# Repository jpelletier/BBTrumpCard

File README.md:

The Big Beautiful Trump Card is a clone of Steve Ciarcia's Trump Card based on the Zilog Z8001 CPU.
The project is released under OSHW.

To simplify the project, I use more recent components such as a CPLD to contain the glue logic and a memory chip to replace the dynamic memory.
The project is in the prototype stage for now. The PCB is at version 1, but untested yet.

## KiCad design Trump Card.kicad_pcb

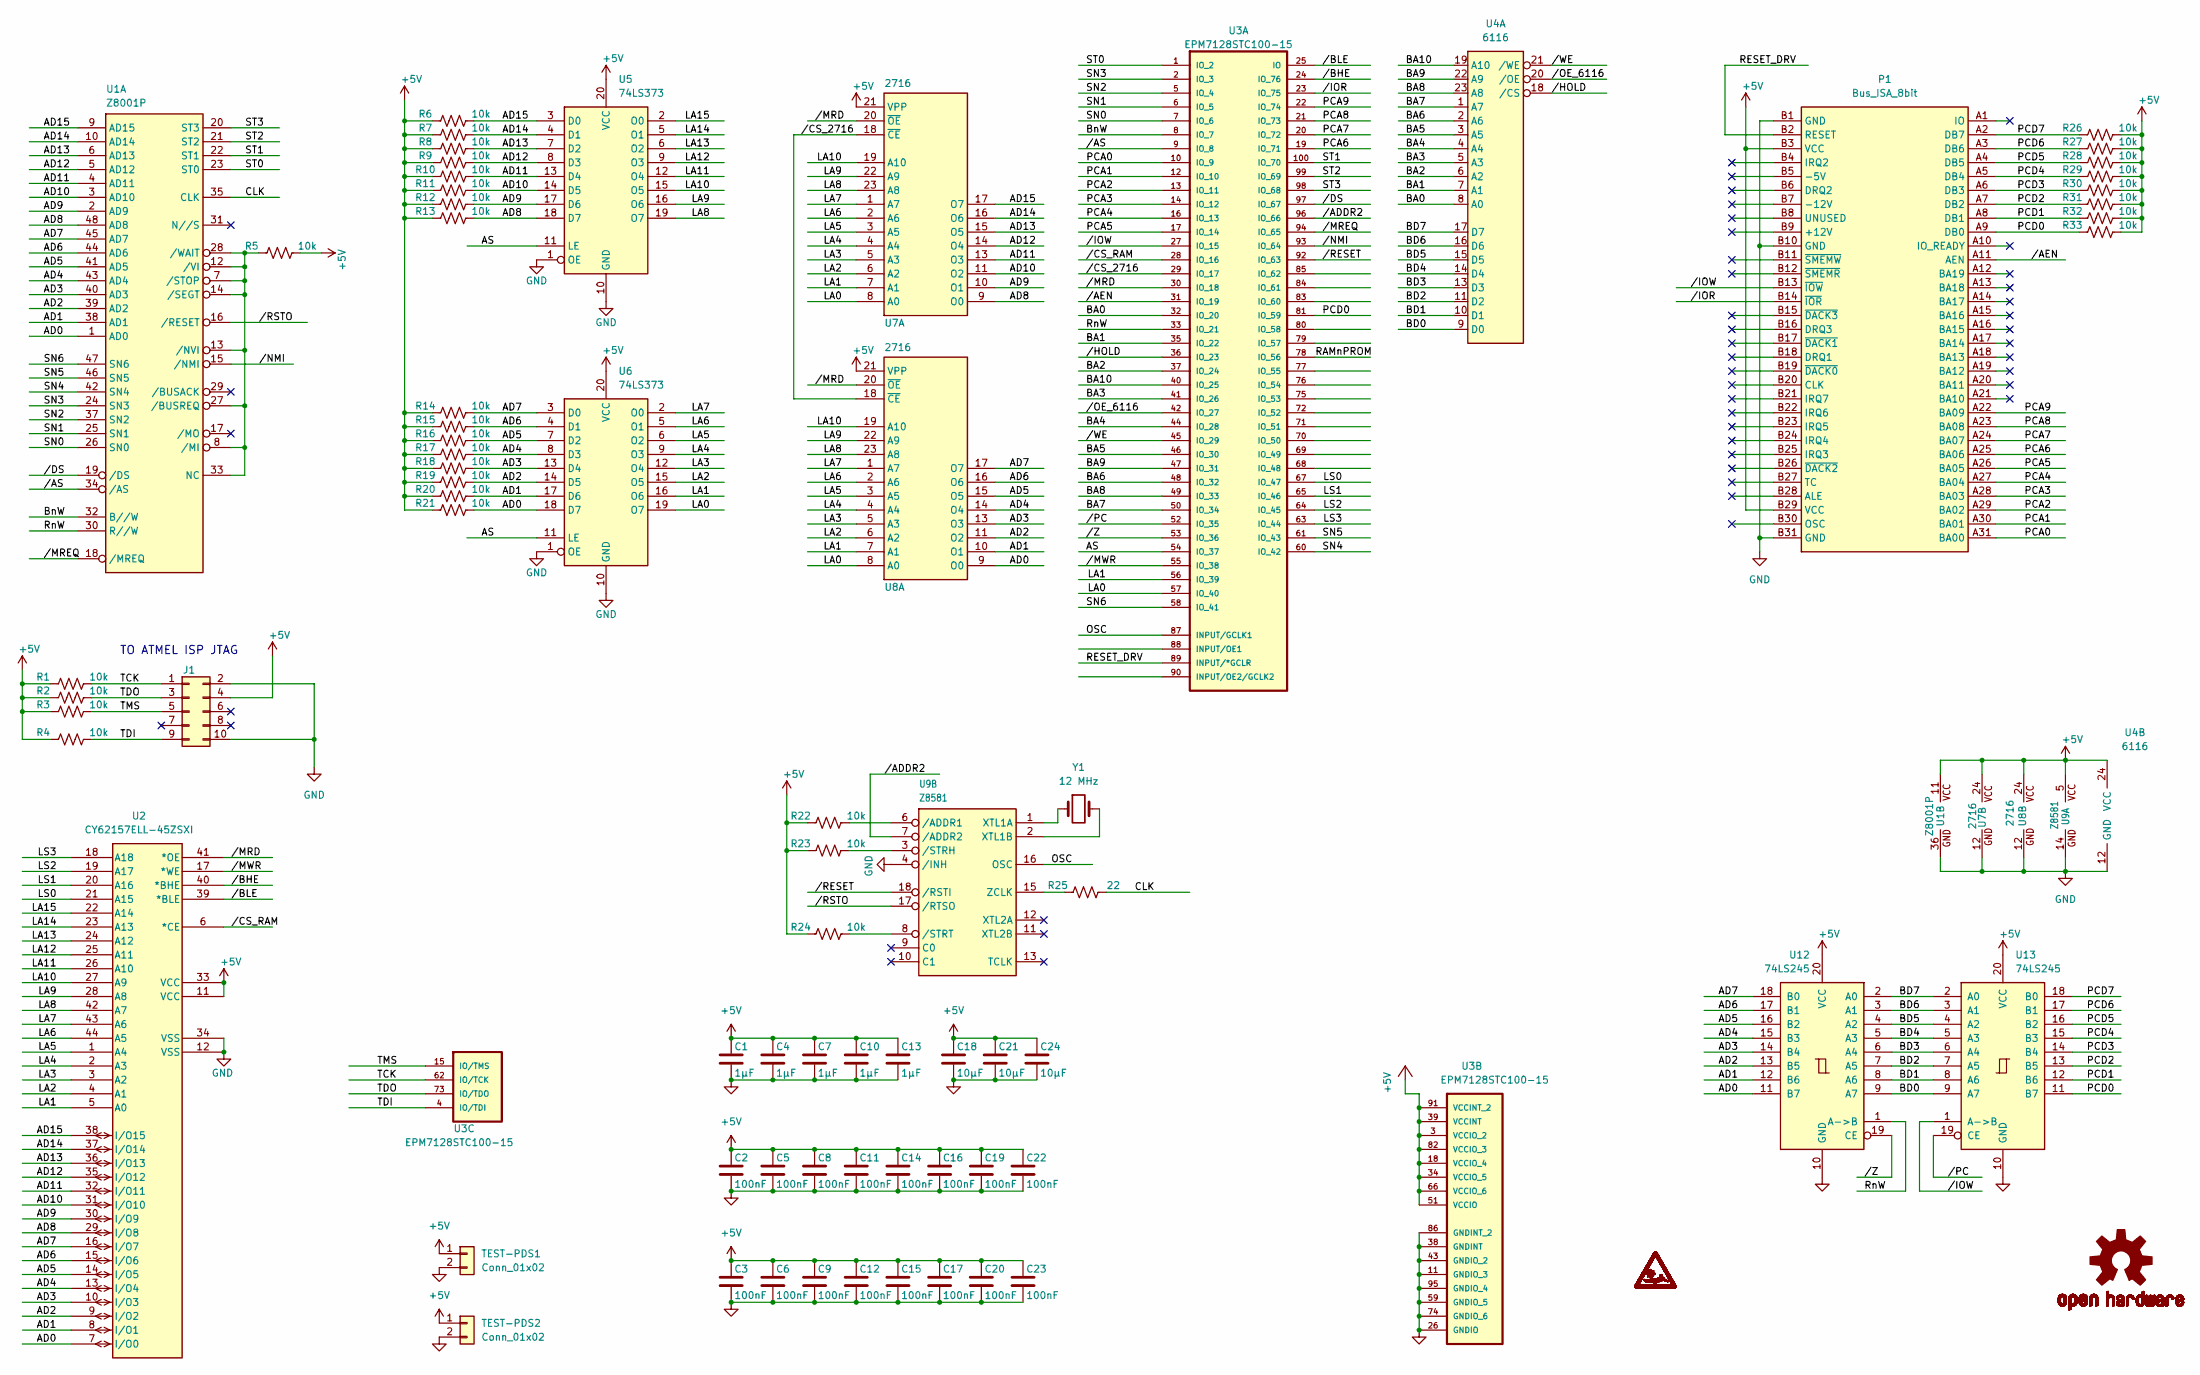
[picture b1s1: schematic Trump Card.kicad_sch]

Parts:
C1, C4, C7, C10, C13: 1µF; C_0805_2012Metric_Pad1.18x1.45mm_HandSolder
C2, C3, C5, C6, C8, C9, C11, C12, C14, C15, C16, C17, C19, C20, C22, C23: 100nF; C_0603_1608Metric_Pad1.08x0.95mm_HandSolder
C18, C21, C24: 10µF; C_0805_2012Metric_Pad1.18x1.45mm_HandSolder
J1: Conn_02x05_Odd_Even; PinHeader_2x05_P2.54mm_Vertical
LOGO1: OSHW-LOGOM; OSHW-LOGO-M
P1: Bus_ISA_8bit; PC-XT-Short-6in
R1, R2, R3, R4, R5, R6, R7, R8, R9, R10, R11, R12, R13, R14, R15, R16, R17, R18, R19, R20, R21, R22, R23, R24, R26, R27, R28, R29, R30, R31, R32, R33: 10k; R_0603_1608Metric_Pad0.98x0.95mm_HandSolder
R25: 22; R_0603_1608Metric_Pad0.98x0.95mm_HandSolder
TEST-PDS1, TEST-PDS2: Conn_01x02; TEST_PDS
U1: Z8001P; DIP-48_W15.24mm
U2: CY62157ELL-45ZSXI; TSOP-II-44_10.16x18.41mm_P0.8mm
U3: EPM7128STC100-15; QFP50P1600X1600X120-100N; MPN EPM7128STC100-15
U4: 6116; DIP-24_18.0mmx34.29mm_W15.24mm
U5, U6: 74LS373; DIP-20_W7.62mm
U7, U8: 2716; DIP-24_18.0mmx34.29mm_W15.24mm
U9: Z8581; DIP-18_W7.62mm
U11: PHYSNOCT_PHYSNOCT; PHYSNOCT
U12, U13: 74LS245; DIP-20_W7.62mm
Y1: 12 MHz; Crystal_HC49-U_Vertical

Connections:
+5V: C1.1, C2.1, C3.1, C4.1, C5.1, C6.1, C7.1, C8.1, C9.1, C10.1, C11.1, C12.1, C13.1, C14.1, C15.1, C16.1, C17.1, C18.1, C19.1, C20.1, C21.1, C22.1, C23.1, C24.1, J1.4, P1.B3 (VCC), P1.B29 (VCC), R1.1, R2.1, R3.1, R4.1, R5.2, R6.1, R7.1, R8.1, R9.1, R10.1, R11.1, R12.1, R13.1, R14.1, R15.1, R16.1, R17.1, R18.1, R19.1, R20.1, R21.1, R22.1, R23.1, R24.1, R26.2, R27.2, R28.2, R29.2, R30.2, R31.2, R32.2, R33.2, TEST-PDS1.1, TEST-PDS2.1, U1.11 (VCC), U2.11 (VCC), U2.33 (VCC), U3.3 (VCCIO_2), U3.18 (VCCIO_4), U3.34 (VCCIO_5), U3.39 (VCCINT), U3.51 (VCCIO), U3.66 (VCCIO_6), U3.82 (VCCIO_3), U3.91 (VCCINT_2), U4.24 (VCC), U5.20 (VCC), U6.20 (VCC), U7.21 (VPP), U7.24 (VCC), U8.21 (VPP), U8.24 (VCC), U9.5 (VCC), U12.20 (VCC), U13.20 (VCC)
/AD0: R21.2, U1.1 (AD0), U2.7 (I/O0), U6.18 (D7), U8.9 (O0), U12.11 (B7)
/AD1: R20.2, U1.38 (AD1), U2.8 (I/O1), U6.17 (D6), U8.10 (O1), U12.12 (B6)
/AD2: R19.2, U1.39 (AD2), U2.9 (I/O2), U6.14 (D5), U8.11 (O2), U12.13 (B5)
/AD3: R18.2, U1.40 (AD3), U2.10 (I/O3), U6.13 (D4), U8.13 (O3), U12.14 (B4)
/AD4: R17.2, U1.43 (AD4), U2.13 (I/O4), U6.8 (D3), U8.14 (O4), U12.15 (B3)
/AD5: R16.2, U1.41 (AD5), U2.14 (I/O5), U6.7 (D2), U8.15 (O5), U12.16 (B2)
/AD6: R15.2, U1.44 (AD6), U2.15 (I/O6), U6.4 (D1), U8.16 (O6), U12.17 (B1)
/AD7: R14.2, U1.45 (AD7), U2.16 (I/O7), U6.3 (D0), U8.17 (O7), U12.18 (B0)
/AD8: R13.2, U1.48 (AD8), U2.29 (I/O8), U5.18 (D7), U7.9 (O0)
/AD9: R12.2, U1.2 (AD9), U2.30 (I/O9), U5.17 (D6), U7.10 (O1)
/AD10: R11.2, U1.3 (AD10), U2.31 (I/O10), U5.14 (D5), U7.11 (O2)
/AD11: R10.2, U1.4 (AD11), U2.32 (I/O11), U5.13 (D4), U7.13 (O3)
/AD12: R9.2, U1.5 (AD12), U2.35 (I/O12), U5.8 (D3), U7.14 (O4)
/AD13: R8.2, U1.6 (AD13), U2.36 (I/O13), U5.7 (D2), U7.15 (O5)
/AD14: R7.2, U1.10 (AD14), U2.37 (I/O14), U5.4 (D1), U7.16 (O6)
/AD15: R6.2, U1.9 (AD15), U2.38 (I/O15), U5.3 (D0), U7.17 (O7)
/AS: U3.54 (IO_37), U5.11 (LE), U6.11 (LE)
/BA0: U3.32 (IO_20), U4.8 (A0)
/BA1: U3.35 (IO_22), U4.7 (A1)
/BA2: U3.37 (IO_24), U4.6 (A2)
/BA3: U3.41 (IO_26), U4.5 (A3)
/BA4: U3.44 (IO_28), U4.4 (A4)
/BA5: U3.46 (IO_30), U4.3 (A5)
/BA6: U3.48 (IO_32), U4.2 (A6)
/BA7: U3.50 (IO_34), U4.1 (A7)
/BA8: U3.49 (IO_33), U4.23 (A8)
/BA9: U3.47 (IO_31), U4.22 (A9)
/BA10: U3.40 (IO_25), U4.19 (A10)
/BD0: U4.9 (D0), U12.9 (A7), U13.9 (A7)
/BD1: U4.10 (D1), U12.8 (A6), U13.8 (A6)
/BD2: U4.11 (D2), U12.7 (A5), U13.7 (A5)
/BD3: U4.13 (D3), U12.6 (A4), U13.6 (A4)
/BD4: U4.14 (D4), U12.5 (A3), U13.5 (A3)
/BD5: U4.15 (D5), U12.4 (A2), U13.4 (A2)
/BD6: U4.16 (D6), U12.3 (A1), U13.3 (A1)
/BD7: U4.17 (D7), U12.2 (A0), U13.2 (A0)
/BnW: U1.32 (B//W), U3.8 (IO_7)
/CLK: R25.2, U1.35 (CLK)
/LA0: U3.57 (IO_40), U6.19 (O7), U7.8 (A0), U8.8 (A0)
/LA1: U2.5 (A0), U3.56 (IO_39), U6.16 (O6), U7.7 (A1), U8.7 (A1)
/LA2: U2.4 (A1), U6.15 (O5), U7.6 (A2), U8.6 (A2)
/LA3: U2.3 (A2), U6.12 (O4), U7.5 (A3), U8.5 (A3)
/LA4: U2.2 (A3), U6.9 (O3), U7.4 (A4), U8.4 (A4)
/LA5: U2.1 (A4), U6.6 (O2), U7.3 (A5), U8.3 (A5)
/LA6: U2.44 (A5), U6.5 (O1), U7.2 (A6), U8.2 (A6)
/LA7: U2.43 (A6), U6.2 (O0), U7.1 (A7), U8.1 (A7)
/LA8: U2.42 (A7), U5.19 (O7), U7.23 (A8), U8.23 (A8)
/LA9: U2.28 (A8), U5.16 (O6), U7.22 (A9), U8.22 (A9)
/LA10: U2.27 (A9), U5.15 (O5), U7.19 (A10), U8.19 (A10)
/LA11: U2.26 (A10), U5.12 (O4)
/LA12: U2.25 (A11), U5.9 (O3)
/LA13: U2.24 (A12), U5.6 (O2)
/LA14: U2.23 (A13), U5.5 (O1)
/LA15: U2.22 (A14), U5.2 (O0)
/LS0: U2.21 (A15), U3.67 (IO_47)
/LS1: U2.20 (A16), U3.65 (IO_46)
/LS2: U2.19 (A17), U3.64 (IO_45)
/LS3: U2.18 (A18), U3.63 (IO_44)
/OSC: U3.87 (INPUT/GCLK1), U9.16 (OSC)
/PCA0: P1.A31 (BA00), U3.10 (IO_9)
/PCA1: P1.A30 (BA01), U3.12 (IO_10)
/PCA2: P1.A29 (BA02), U3.13 (IO_11)
/PCA3: P1.A28 (BA03), U3.14 (IO_12)
/PCA4: P1.A27 (BA04), U3.16 (IO_13)
/PCA5: P1.A26 (BA05), U3.17 (IO_14)
/PCA6: P1.A25 (BA06), U3.19 (IO_71)
/PCA7: P1.A24 (BA07), U3.20 (IO_72)
/PCA8: P1.A23 (BA08), U3.21 (IO_73)
/PCA9: P1.A22 (BA09), U3.22 (IO_74)
/PCD0: P1.A9 (DB0), R33.1, U3.81 (IO_59), U13.11 (B7)
/PCD1: P1.A8 (DB1), R32.1, U13.12 (B6)
/PCD2: P1.A7 (DB2), R31.1, U13.13 (B5)
/PCD3: P1.A6 (DB3), R30.1, U13.14 (B4)
/PCD4: P1.A5 (DB4), R29.1, U13.15 (B3)
/PCD5: P1.A4 (DB5), R28.1, U13.16 (B2)
/PCD6: P1.A3 (DB6), R27.1, U13.17 (B1)
/PCD7: P1.A2 (DB7), R26.1, U13.18 (B0)
/RAMnPROM: U3.78 (IO_56)
/RESET_DRV: P1.B2 (RESET), U3.89 (INPUT/*GCLR)
/RnW: U1.30 (R//W), U3.33 (IO_21), U12.1 (A->B)
/SN0: U1.26 (SN0), U3.7 (IO_6)
/SN1: U1.25 (SN1), U3.6 (IO_5)
/SN2: U1.37 (SN2), U3.5 (IO_4)
/SN3: U1.24 (SN3), U3.2 (IO_3)
/SN4: U1.42 (SN4), U3.60 (IO_42)
/SN5: U1.46 (SN5), U3.61 (IO_43)
/SN6: U1.47 (SN6), U3.58 (IO_41)
/ST0: U1.23 (ST0), U3.1 (IO_2)
/ST1: U1.22 (ST1), U3.100 (IO_70)
/ST2: U1.21 (ST2), U3.99 (IO_69)
/ST3: U1.20 (ST3), U3.98 (IO_68)
/TCK: J1.1, R1.2, U3.62 (IO/TCK)
/TDI: J1.9, R4.2, U3.4 (IO/TDI)
/TDO: J1.3, R2.2, U3.73 (IO/TDO)
/TMS: J1.5, R3.2, U3.15 (IO/TMS)
//ADDR2: U3.96 (IO_66), U9.7 (/ADDR2)
//AEN: P1.A11 (AEN), U3.31 (IO_19)
//AS: U1.34 (/AS), U3.9 (IO_8)
//BHE: U2.40 (*BHE), U3.24 (IO_76)
//BLE: U2.39 (*BLE), U3.25 (IO)
//CS_2716: U3.29 (IO_17), U7.18 (~CE), U8.18 (~CE)
//CS_RAM: U2.6 (*CE), U3.28 (IO_16)
//DS: U1.19 (/DS), U3.97 (IO_67)
//HOLD: U3.36 (IO_23), U4.18 (/CS)
//IOR: P1.B14 (~IOR), U3.23 (IO_75)
//IOW: P1.B13 (~IOW), U3.27 (IO_15), U13.1 (A->B)
//MRD: U2.41 (*OE), U3.30 (IO_18), U7.20 (~OE), U8.20 (~OE)
//MREQ: U1.18 (/MREQ), U3.94 (IO_65)
//MWR: U2.17 (*WE), U3.55 (IO_38)
//NMI: U1.15 (/NMI), U3.93 (IO_64)
//OE_6116: U3.42 (IO_27), U4.20 (/OE)
//PC: U3.52 (IO_35), U13.19 (CE)
//RESET: U3.92 (IO_63), U9.18 (/RSTI)
//RSTO: U1.16 (/RESET), U9.17 (/RTSO)
//WE: U3.45 (IO_29), U4.21 (/WE)
//Z: U3.53 (IO_36), U12.19 (CE)
GND: C1.2, C2.2, C3.2, C4.2, C5.2, C6.2, C7.2, C8.2, C9.2, C10.2, C11.2, C12.2, C13.2, C14.2, C15.2, C16.2, C17.2, C18.2, C19.2, C20.2, C21.2, C22.2, C23.2, C24.2, J1.2, J1.10, P1.B1 (GND), P1.B10 (GND), P1.B31 (GND), TEST-PDS1.2, TEST-PDS2.2, U1.36 (GND), U2.12 (VSS), U2.34 (VSS), U3.11 (GNDIO_3), U3.26 (GNDIO), U3.38 (GNDINT), U3.43 (GNDIO_2), U3.59 (GNDIO_5), U3.74 (GNDIO_6), U3.86 (GNDINT_2), U3.95 (GNDIO_4), U4.12 (GND), U5.1 (OE), U5.10 (GND), U6.1 (OE), U6.10 (GND), U7.12 (GND), U8.12 (GND), U9.4 (/INH), U9.14 (GND), U12.10 (GND), U13.10 (GND)
unnamed: R5.1, U1.7 (/STOP), U1.8 (/MI), U1.12 (/VI), U1.13 (/NVI), U1.14 (/SEGT), U1.27 (/BUSREQ), U1.28 (/WAIT), U1.33 (NC)
unnamed: U9.1 (XTL1A), Y1.1
unnamed: U9.2 (XTL1B), Y1.2
unnamed: R25.1, U9.15 (ZCLK)
unnamed: R22.2, U9.6 (/ADDR1)
unnamed: R23.2, U9.3 (/STRH)
unnamed: R24.2, U9.8 (/STRT)

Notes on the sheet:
TO ATMEL ISP JTAG

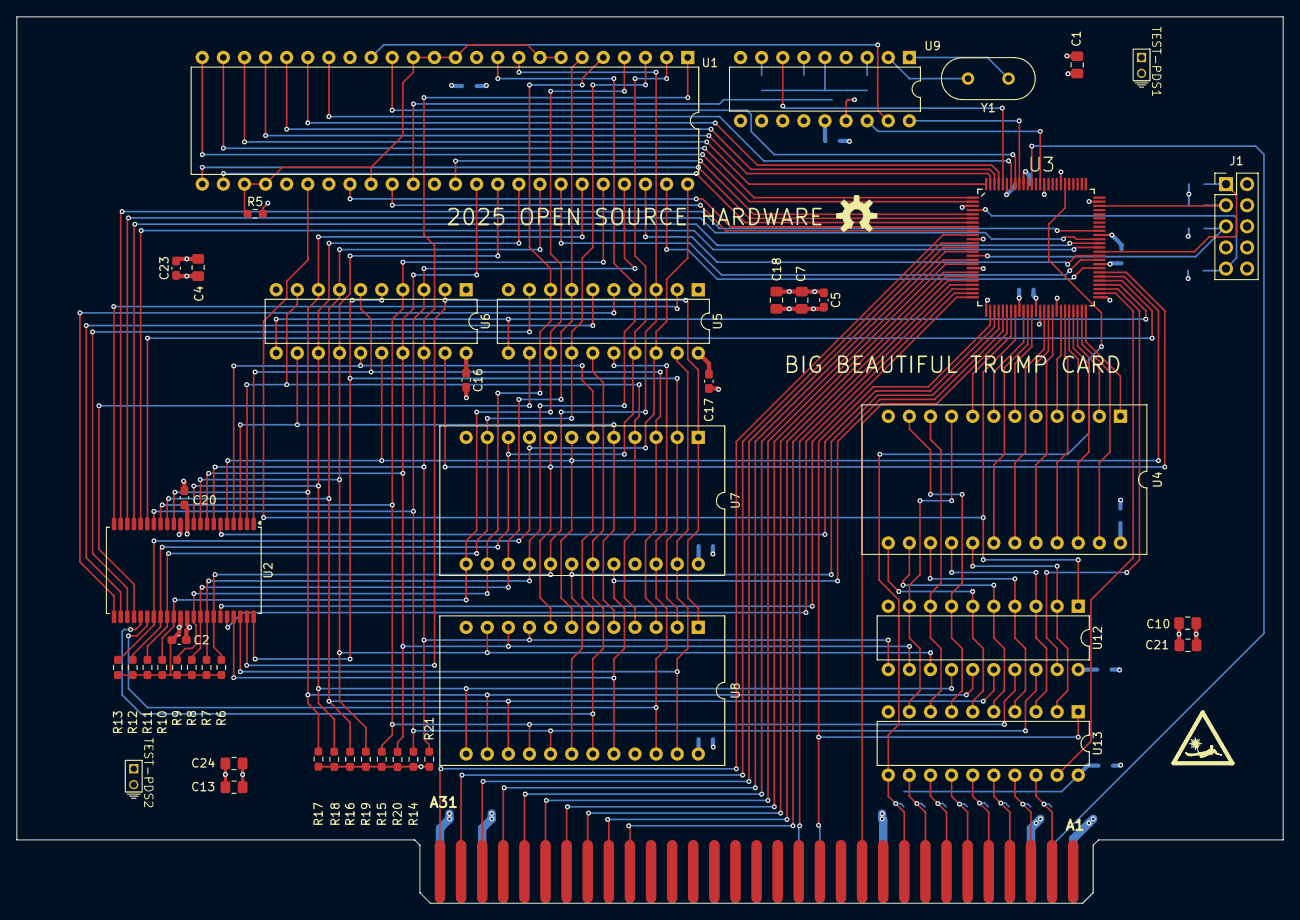
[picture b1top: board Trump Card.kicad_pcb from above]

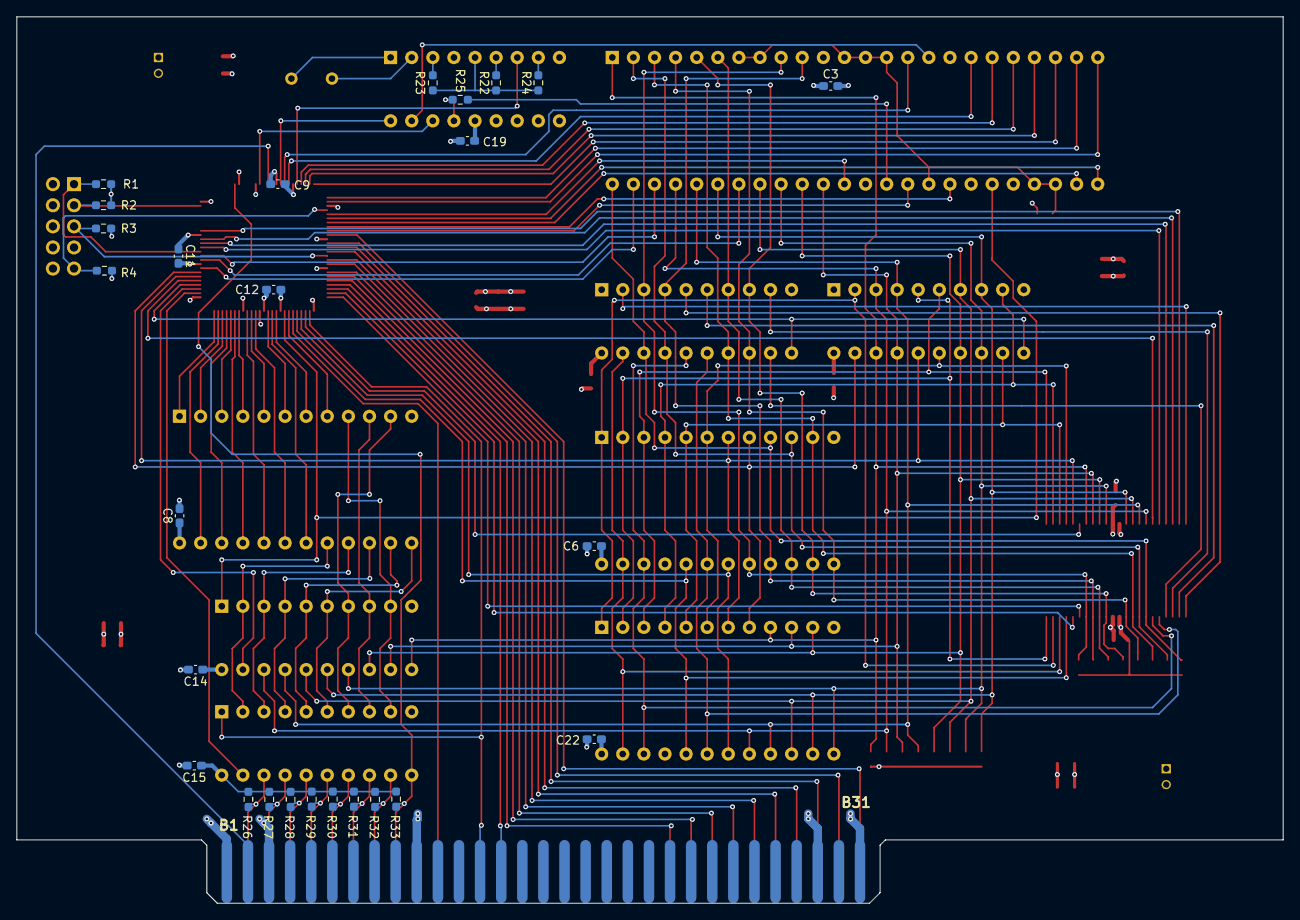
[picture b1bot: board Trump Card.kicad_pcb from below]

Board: 4 copper layers, 152.4 x 106.7 mm, 75 parts (26 on the bottom side), 124 nets.

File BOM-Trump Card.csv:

"Reference","Value","Qty","MPN","PACKAGE","SUPPLIER","Description","Manufacturer","Supplier2 Part Number","Supplier Part Number","SUPPLIER2"
"C1,C4,C7,C10,C13","1µF","5",,"0805",,"Unpolarized capacitor",,,,
"C2,C3,C5,C6,C8,C9,C11,C12,C14,C15,C16,C17,C19,C20,C22,C23","100nF","16",,"0603",,"Unpolarized capacitor",,,,
"C18,C21,C24","10µF","3",,"0805",,"Unpolarized capacitor",,,,
"J1","Conn_02x05_Odd_Even","1",,,"Digikey, AliExpress, eBay","Generic connector, double row, 02x05, odd/even pin numbering scheme (row 1 odd numbers, row 2 even numbers), script generated (kicad-library-utils/schlib/autogen/connector/)",,,,
"R1,R2,R3,R4,R5,R6,R7,R8,R9,R10,R11,R12,R13,R14,R15,R16,R17,R18,R19,R20,R21,R22,R23,R24,R26,R27,R28,R29,R30,R31,R32,R33","10k","32",,"0603",,"Resistor, US symbol",,,,
"R25","22","1",,"0603",,"Resistor, US symbol",,,,
"U1","Z8001P","1",,"DIP-48","eBay","CPU",,,,
"U2","CY62157ELL-45ZSXI","1",,"TSOP-II-44","Digikey",,"Infineon","2767919","448-CY62157ELL-45ZSXI-ND","Farnell UK"
"U3","EPM7128STC100-15","1","EPM7128STC100-15","1100-TQFP","AliExpress, eBay",,"Altera/Intel",,,
"U4","6116","1",,"DIP-24","eBay, AliExpress",,,,,
"U5,U6","74LS373","2",,"DIP-20","Digikey, AliExpress, eBay","8-bit Latch, 3-state outputs",,,,
"U7,U8","2716","2",,"DIP-24","-- valeurs mixées --",,,,,
"U9","Z8581","1",,"DIP-18","AliExpress, eBay",,,,,
"U12,U13","74LS245","2",,"DIP-20","Digikey, AliExpress, eBay","Octal BUS Transceivers, 3-State outputs",,,,
"Y1","12 MHz","1",,"HC49-U","Digikey, AliExpress","Two pin crystal",,,,

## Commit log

2025-08-16 Initial commit
    This project is a clone of the Steve Ciarcia's Trump Card. I nick named it the Big Beautiful Trump Card!
2025-08-18 Changed CPLD to a EPM7128STC100-15
    The new CPLD has more available pins than the Atmel chip, and the programmer is more common and cheaper.
2025-08-18 Initial commit
    Quartus II zipped project for the BBTC's CPLD
2025-08-18 Update README.md
    Added OSHW
2025-08-22 Final commit for V1
    Modified the schematic and CPLD assignation to make PCB routing easier,
    PCB completed and gerber files provided.
2025-08-22 Final commit for V1
2025-09-29 Add files via upload
    Updates on component fields to generate BOM
2025-09-29 Delete TrumpCard.zip
    file obsolete
